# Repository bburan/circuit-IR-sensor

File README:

Overview
--------

This is a circuit that provides power for up to 4 infrared
emitter/phototransistor pairs. The photodiode current is converted to voltage
and low-pass filtered cutoff frequency approx. 150 Hz). Holes are designed for
a 4-40 screw (a common size in standoffs). The circuit is designed to work with
the OPS693 phototransistor LED/sensor matched pair. The 3D models of the food
hopper and nose-pokes are designed with the dimensions of the OPS693 in mind.
This requires a 5VDC power supply.

Assembly
--------

Design files generated using KiCAD. The Gerber files can be uploaded to a PCB
manufacturer such as Macrofab. Total cost for a fully assembled circuit from
Macrofab is roughly $15. Once the assembled board arrives, you'll need to
either solder wires directly to the holes or use 0.1" (2.54mm) pitch header
pins. The Pheonix MPT screw terminal blocks also work very well as they have
the same pin spacing.

License
-------

This project is licensed under the Creative Commons Attribution 4.0
International license.

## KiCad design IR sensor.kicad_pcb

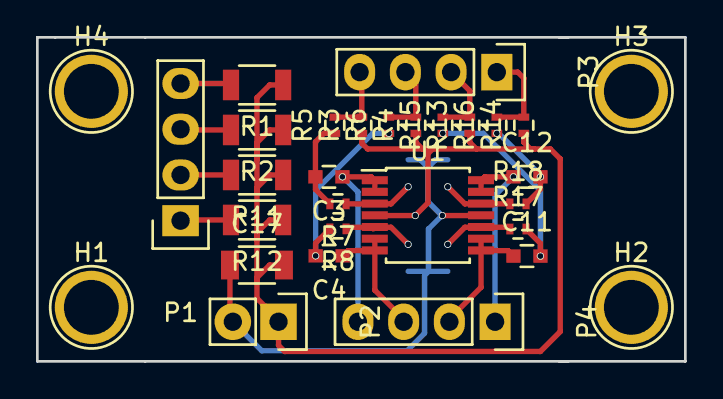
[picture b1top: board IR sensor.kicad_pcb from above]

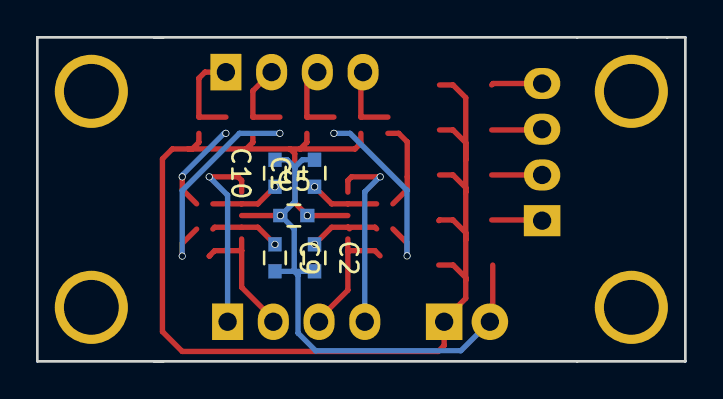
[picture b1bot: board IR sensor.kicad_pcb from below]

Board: 2 copper layers, 36.0 x 18.0 mm, 35 parts (5 on the bottom side), 22 nets.

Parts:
C1, C2, C3, C4, C5, C9, C10, C11, C12: 0.1uF; C_0603
C17: 10uF; C_1206
H1, H2, H3, H4: CONN_01X01; 1pin
P1, P3, P4: CONN_01X04; Pin_Header_Straight_1x04
P2: CONN_01X02; Pin_Header_Straight_1x02
R1, R2, R11, R12: 100 0.25W; R_1206
R3, R4, R5, R6, R7, R8, R13, R14, R15, R16, R17, R18: 10k; R_0402
U1: LM2902; TSSOP-14_4.4x5mm_P0.65mm

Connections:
+5V: C5.2, C17.2, P2.1, R1.1, R2.1, R3.1, R4.1, R11.1, R12.1, R13.1, R14.1, U1.4
E1+: P1.4, R1.2
E2+: P1.3, R2.2
E3+: P1.2, R11.2
E4+: P1.1, R12.2
GND: C1.2, C2.2, C5.1, C9.2, C10.2, C17.1, P2.2, U1.11
unnamed: C1.1, R7.1, U1.3
unnamed: C2.1, R8.1, U1.5
unnamed: C3.2, R5.1, R7.2
unnamed: C4.2, R6.1, R8.2
unnamed: C9.1, R17.1, U1.10
unnamed: C10.1, R18.1, U1.12
unnamed: C11.2, R15.1, R17.2
unnamed: C12.2, R16.1, R18.2
O1: C3.1, P4.4, U1.1, U1.2
O2: C4.1, P4.3, U1.6, U1.7
O3: C11.1, P4.2, U1.8, U1.9
O4: C12.1, P4.1, U1.13, U1.14
S1+: P3.4, R3.2, R5.2
S2+: P3.3, R4.2, R6.2
S3+: P3.2, R13.2, R15.2
S4+: P3.1, R14.2, R16.2

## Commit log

2015-12-18 ENH: Added IR sensor circuit
2016-02-17 ENH: Updates to IR sensors
2017-07-11 ENH: Make PCB more compact
2017-07-11 Add gerber outputs
2017-07-11 Add readme and bill of materials
2017-07-11 Modified readme to add license
2020-01-22 Commit before modifications
2020-01-22 Update to KiCAD 5
